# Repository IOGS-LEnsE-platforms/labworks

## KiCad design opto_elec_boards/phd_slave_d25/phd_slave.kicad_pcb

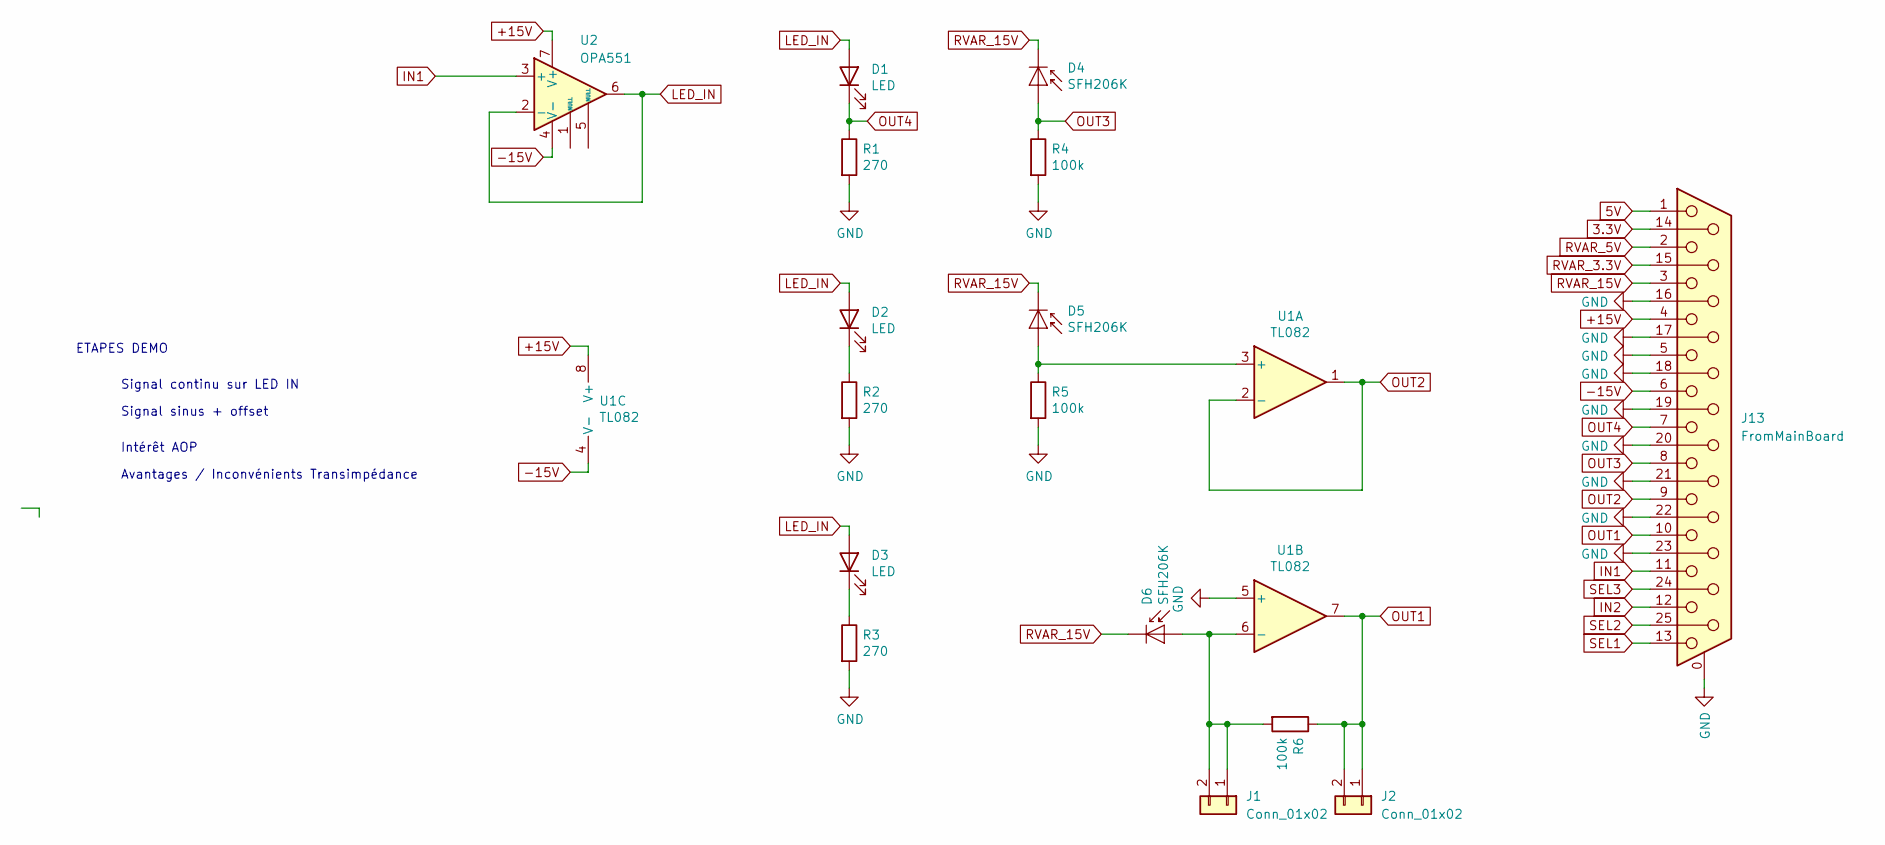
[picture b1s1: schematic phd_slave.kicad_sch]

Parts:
D1, D2, D3: LED; LED_D5.0mm_Horizontal_O3.81mm_Z9.0mm
D4, D5, D6: SFH206K; Osram_SFH206_2
J1, J2: Conn_01x02; PinSocket_1x02_P2.54mm_Vertical
J13: FromMainBoard; DSUB-25_Socket_Horizontal_P2.77x2.84mm_EdgePinOffset7.70mm_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
R1, R2, R3: 270; R_Axial_DIN0309_L9.0mm_D3.2mm_P12.70mm_Horizontal
R4, R5, R6: 100k; R_Axial_DIN0309_L9.0mm_D3.2mm_P12.70mm_Horizontal
U1: TL082; DIP-8_W7.62mm_LongPads
U2: OPA551; DIP-8_W7.62mm_LongPads

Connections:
3.3V: J13.14
5V: J13.1
+15V: J13.4, U1.8 (V+), U2.7 (V+)
-15V: J13.6, U1.4 (V-), U2.4 (V-)
GND: J13.0 (PAD), J13.5, J13.16, J13.17, J13.18, J13.19, J13.20, J13.21, J13.22, J13.23, R1.2, R2.2, R3.2, R4.2, R5.2, U1.5 (+)
IN1: J13.11, U2.3 (+)
IN2: J13.12
LED_IN: D1.2 (A), D2.2 (A), D3.2 (A), U2.2 (-), U2.6
unnamed: D2.1 (K), R2.1
unnamed: D3.1 (K), R3.1
unnamed: D5.2 (A), R5.1, U1.3 (+)
unnamed: D6.2 (A), J1.1, J1.2, R6.2, U1.6 (-)
OUT1: J2.1, J2.2, J13.10, R6.1, U1.7
OUT2: J13.9, U1.1, U1.2 (-)
OUT3: D4.2 (A), J13.8, R4.1
OUT4: D1.1 (K), J13.7, R1.1
RVAR_3.3V: J13.15
RVAR_5V: J13.2
RVAR_15V: D4.1 (K), D5.1 (K), D6.1 (K), J13.3
SEL1: J13.13
SEL2: J13.25
SEL3: J13.24

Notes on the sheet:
Signal continu sur LED IN
ETAPES DEMO
Intérêt AOP
Avantages / Inconvénients Transimpédance
Signal sinus + offset

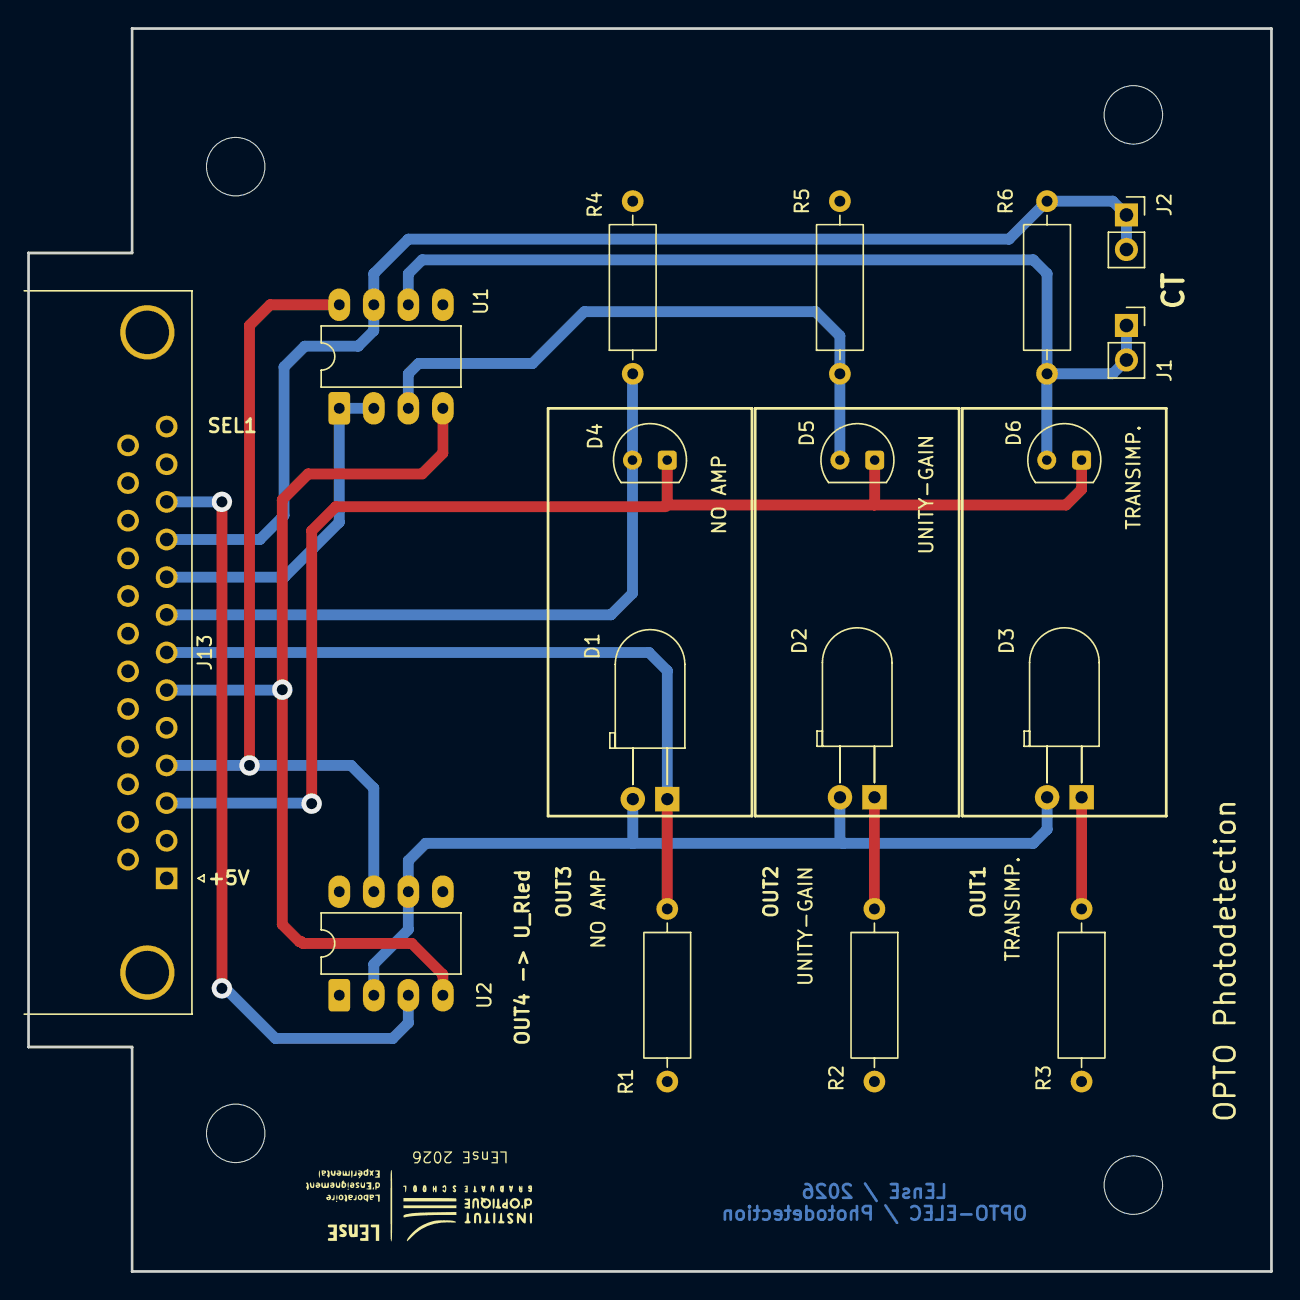
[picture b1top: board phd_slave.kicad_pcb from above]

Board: 2 copper layers, 91.4 x 91.4 mm, 21 parts (0 on the bottom side), 14 nets.

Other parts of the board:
M4a, M4b, M4c, M4d: MountingHole_4.3mm_M4

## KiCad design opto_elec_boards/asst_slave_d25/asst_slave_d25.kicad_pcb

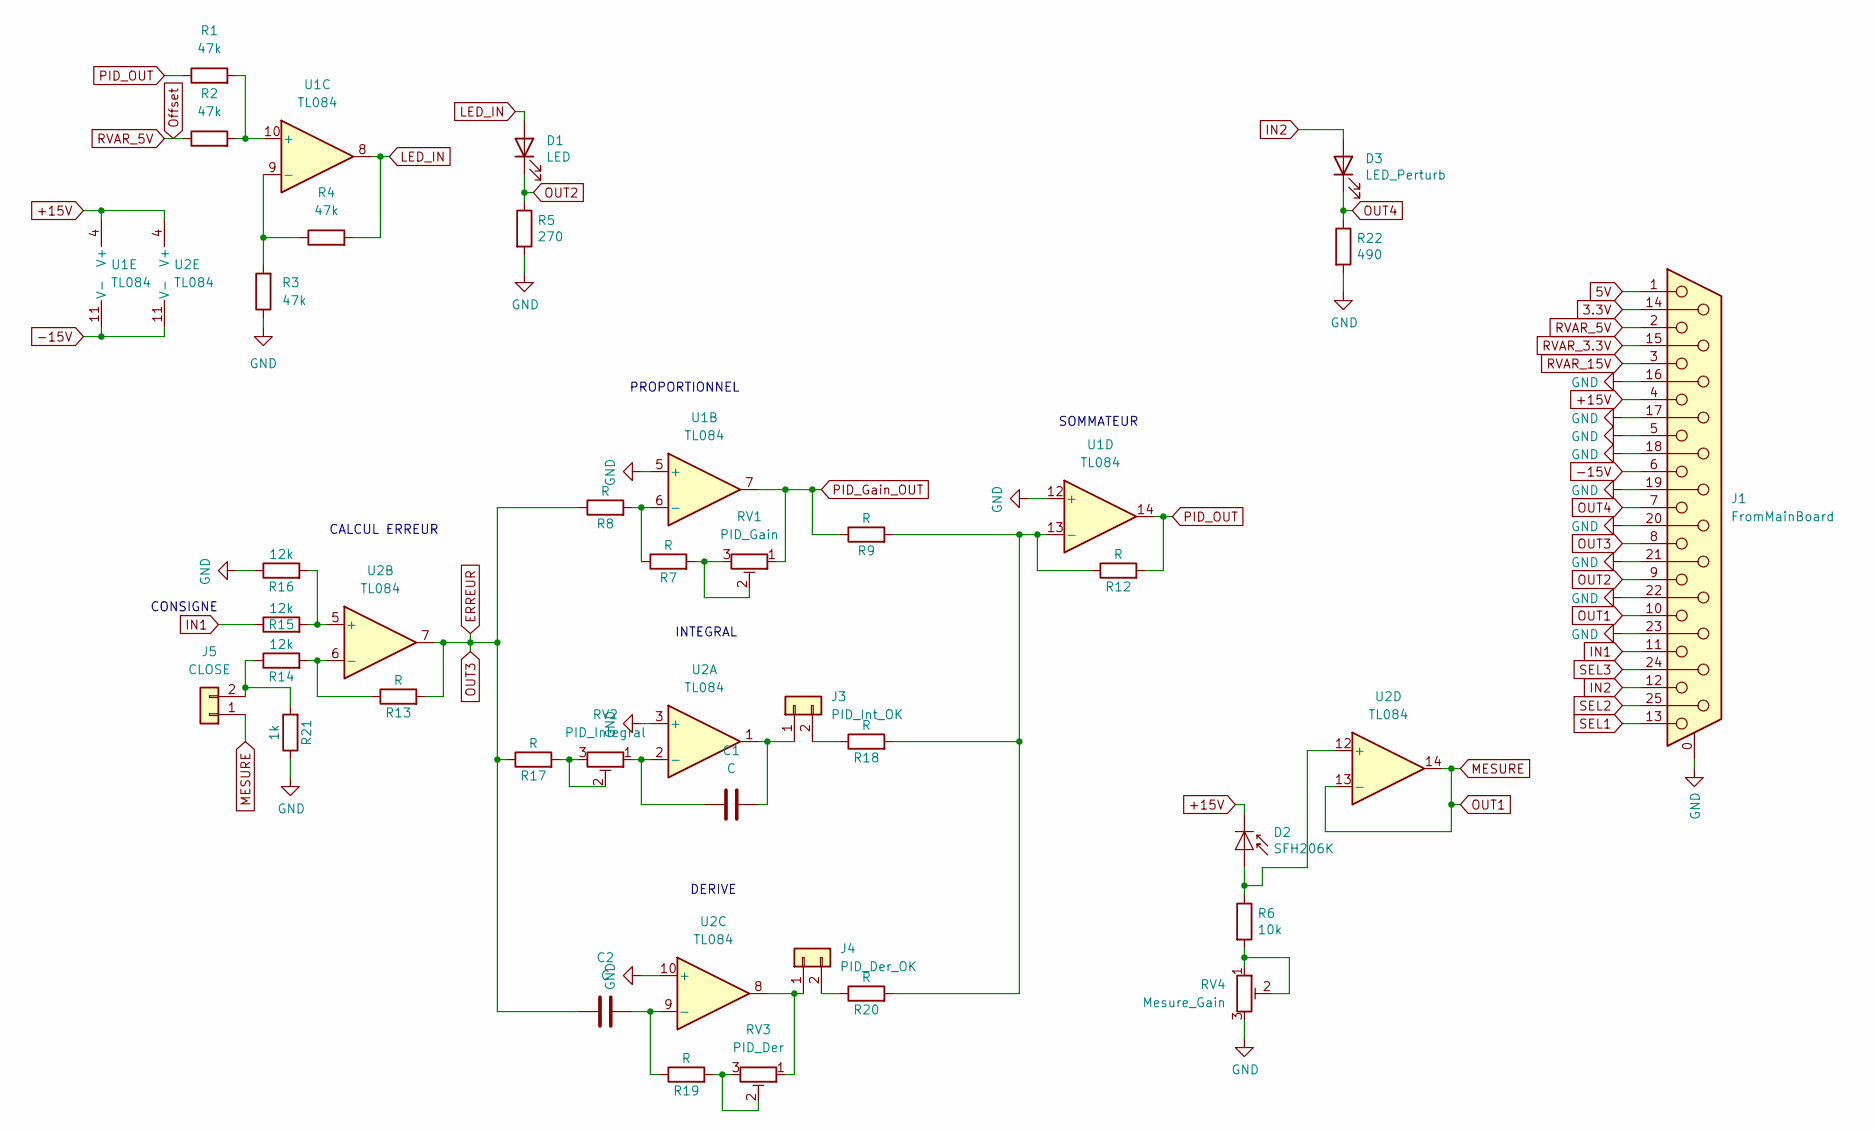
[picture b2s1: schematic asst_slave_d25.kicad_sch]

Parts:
C1, C2: C; C_R_Multi
D1: LED; LED_D10.0mm
D2: SFH206K; Osram_SFH206_2
D3: LED_Perturb; LED_D5.0mm_Horizontal_O3.81mm_Z9.0mm
J1: FromMainBoard; DSUB-25_Socket_Horizontal_P2.77x2.84mm_EdgePinOffset7.70mm_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
J3: PID_Int_OK; PinSocket_1x02_P2.54mm_Vertical
J4: PID_Der_OK; PinSocket_1x02_P2.54mm_Vertical
J5: CLOSE; PinSocket_1x02_P2.54mm_Vertical
R1, R2, R3, R4: 47k; R_Axial_DIN0207_L6.3mm_D2.5mm_P10.16mm_Horizontal
R5: 270; R_Axial_DIN0207_L6.3mm_D2.5mm_P10.16mm_Horizontal
R6: 10k; R_Axial_DIN0207_L6.3mm_D2.5mm_P10.16mm_Horizontal
R7, R8, R9, R12, R13, R17, R18, R19, R20: R; R_Axial_DIN0207_L6.3mm_D2.5mm_P10.16mm_Horizontal
R14, R15, R16: 12k; R_Axial_DIN0207_L6.3mm_D2.5mm_P10.16mm_Horizontal
R21: 1k; R_Axial_DIN0207_L6.3mm_D2.5mm_P10.16mm_Horizontal
R22: 490; R_Axial_DIN0207_L6.3mm_D2.5mm_P10.16mm_Horizontal
RV1: PID_Gain; Potentiometer_Bourns_3386P_Vertical
RV2: PID_Integral; Potentiometer_Bourns_3386P_Vertical
RV3: PID_Der; Potentiometer_Bourns_3386P_Vertical
RV4: Mesure_Gain; Potentiometer_Bourns_3386P_Vertical
U1, U2: TL084; DIP-14_W7.62mm_Socket_LongPads

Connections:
3.3V: J1.14
5V: J1.1
+15V: D2.1 (K), J1.4, U1.4 (V+), U2.4 (V+)
-15V: J1.6, U1.11 (V-), U2.11 (V-)
ERREUR: C2.1, J1.8, R8.1, R13.2, R17.1, U2.7
GND: J1.0 (PAD), J1.5, J1.16, J1.17, J1.18, J1.19, J1.20, J1.21, J1.22, J1.23, R3.1, R5.2, R16.1, R21.1, R22.2, RV4.3, U1.5 (+), U1.12 (+), U2.3 (+), U2.10 (+)
IN1: J1.11, R15.1
IN2: D3.2 (A), J1.12
LED_IN: D1.2 (A), R4.2, U1.8
MESURE: J1.10, J5.1, U2.13 (-), U2.14
unnamed: D2.2 (A), R6.1, U2.12 (+)
unnamed: C1.2, J3.1, U2.1
unnamed: J3.2, R18.1
unnamed: J4.1, RV3.1, U2.8
unnamed: J4.2, R20.1
unnamed: J5.2, R14.1, R21.2
unnamed: R6.2, RV4.1, RV4.2
unnamed: R7.2, RV1.2, RV1.3
unnamed: R17.2, RV2.2, RV2.3
unnamed: R19.2, RV3.2, RV3.3
unnamed: R7.1, R8.2, U1.6 (-)
unnamed: R1.2, R2.2, U1.10 (+)
unnamed: R3.2, R4.1, U1.9 (-)
unnamed 24: R9.2, R12.1, R18.2, R20.2, U1.13 (-); also elsewhere on the board
unnamed: C1.1, RV2.1, U2.2 (-)
unnamed: R15.2, R16.2, U2.5 (+)
unnamed: R13.1, R14.2, U2.6 (-)
unnamed: C2.2, R19.1, U2.9 (-)
OUT2: D1.1 (K), J1.9, R5.1
OUT4: D3.1 (K), J1.7, R22.1
Offset: J1.2, R2.1
PID_Gain_OUT: R9.1, RV1.1, U1.7
PID_OUT: R1.1, R12.2, U1.14
RVAR_3.3V: J1.15
RVAR_15V: J1.3
SEL1: J1.13
SEL2: J1.25
SEL3: J1.24

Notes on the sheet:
DERIVE
CALCUL ERREUR
SOMMATEUR
CONSIGNE
INTEGRAL
PROPORTIONNEL

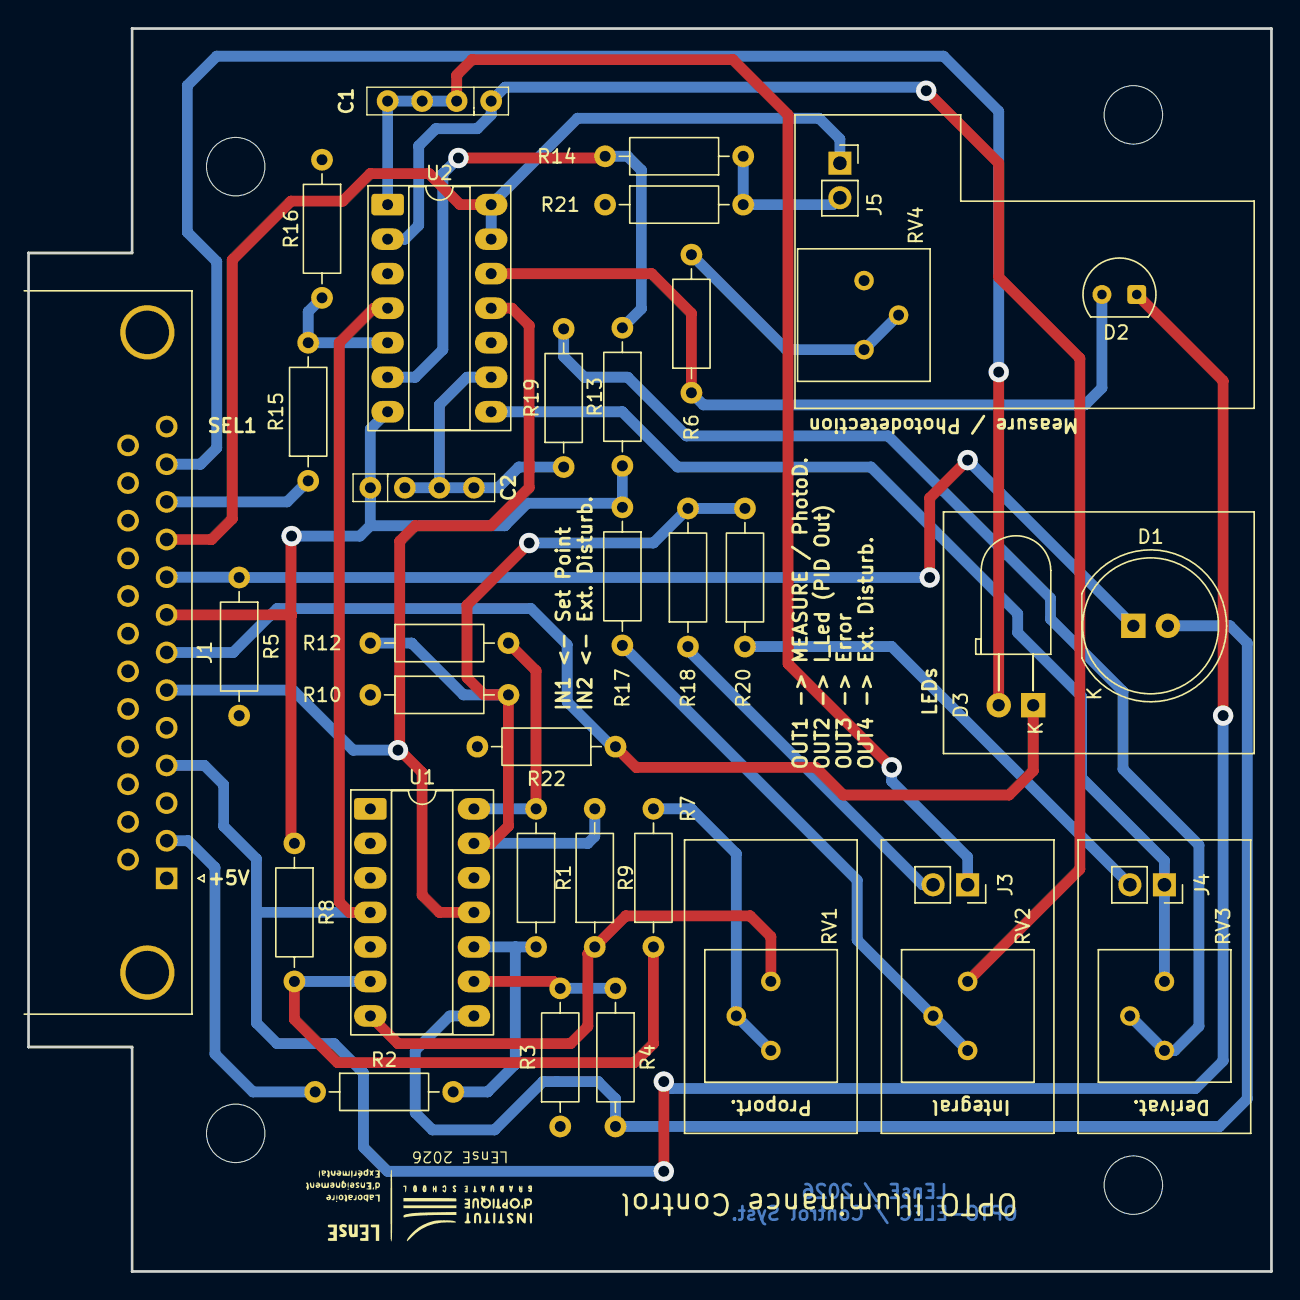
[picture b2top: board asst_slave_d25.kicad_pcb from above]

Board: 2 copper layers, 91.4 x 91.4 mm, 40 parts (0 on the bottom side), 31 nets.

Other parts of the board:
M4a, M4b, M4c, M4d: MountingHole_4.3mm_M4
R10: R; R_Axial_DIN0207_L6.3mm_D2.5mm_P10.16mm_Horizontal

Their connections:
unnamed 24: R10.2; also elsewhere on the board

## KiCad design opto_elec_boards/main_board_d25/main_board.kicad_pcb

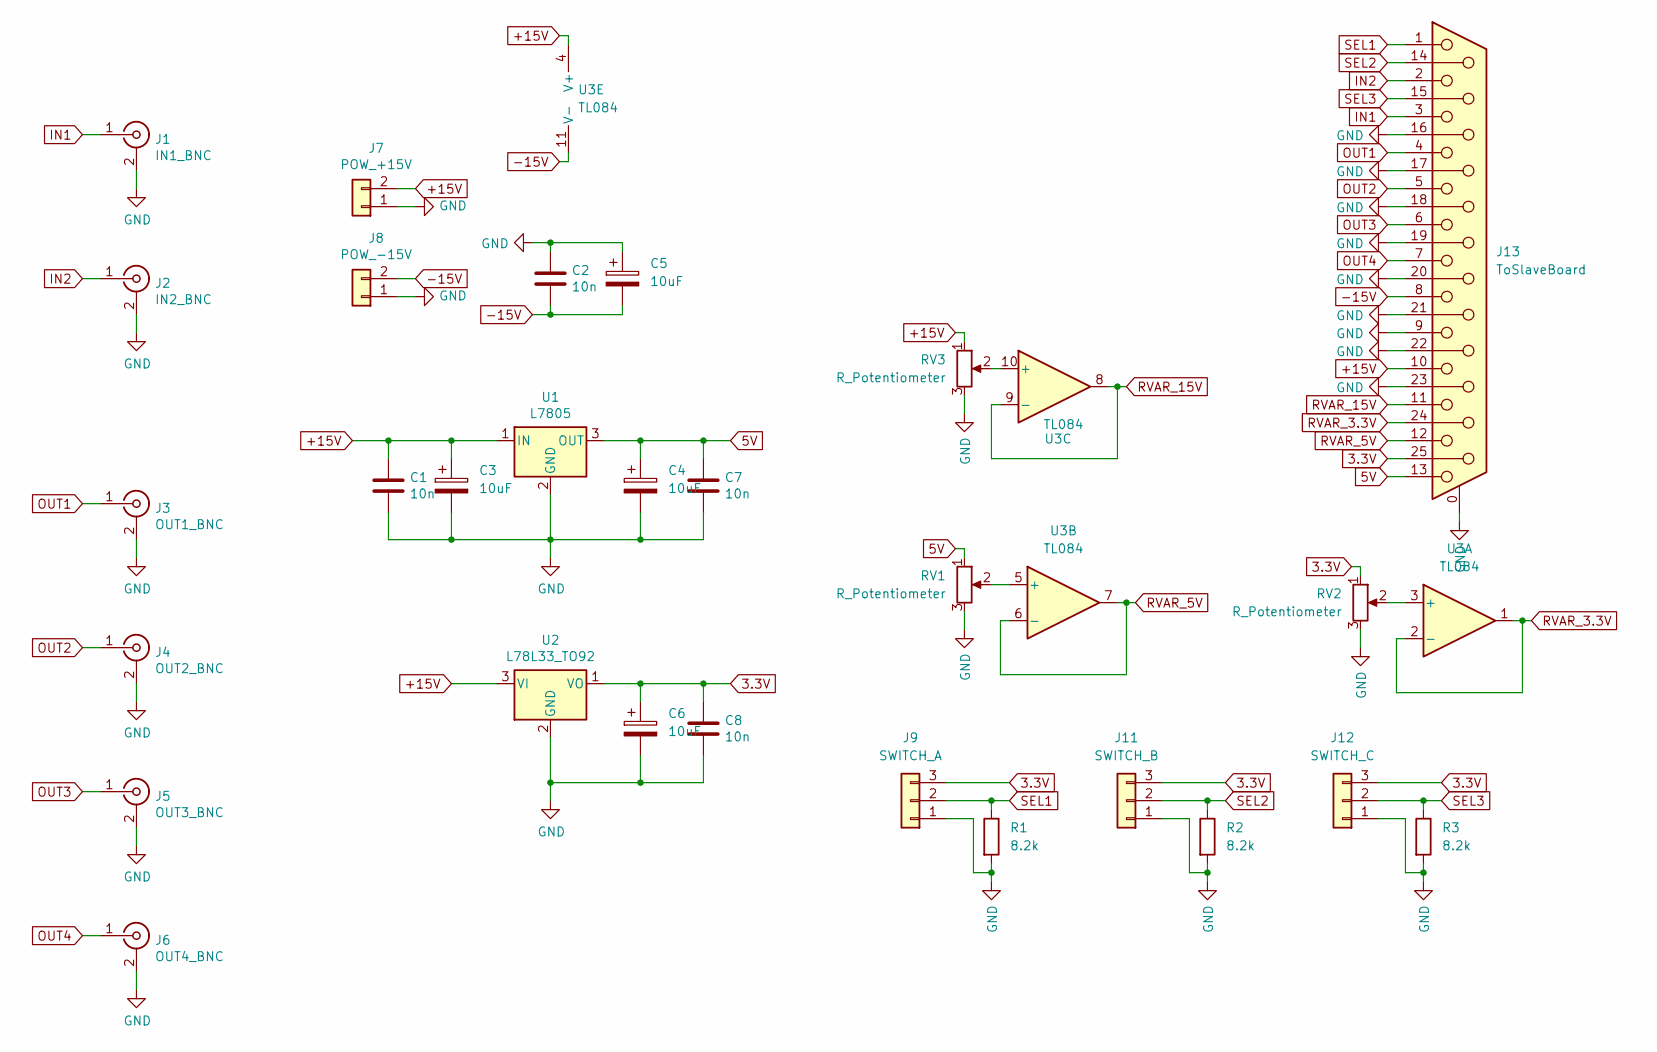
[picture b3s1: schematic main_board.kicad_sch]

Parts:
C1, C2, C7, C8: 10n; C_Disc_D10.0mm_W2.5mm_P5.00mm
C3, C4, C5, C6: 10uF; CP_Radial_D5.0mm_P2.50mm
J1: IN1_BNC; PinHeader_1x02_P2.54mm_Vertical
J2: IN2_BNC; PinHeader_1x02_P2.54mm_Vertical
J3: OUT1_BNC; PinHeader_1x02_P2.54mm_Vertical
J4: OUT2_BNC; PinHeader_1x02_P2.54mm_Vertical
J5: OUT3_BNC; PinHeader_1x02_P2.54mm_Vertical
J6: OUT4_BNC; PinHeader_1x02_P2.54mm_Vertical
J7: POW_+15V; PinSocket_1x02_P2.54mm_Vertical
J8: POW_-15V; PinSocket_1x02_P2.54mm_Vertical
J9: SWITCH_A; PinSocket_1x03_P2.54mm_Vertical
J11: SWITCH_B; PinSocket_1x03_P2.54mm_Vertical
J12: SWITCH_C; PinSocket_1x03_P2.54mm_Vertical
J13: ToSlaveBoard; DSUB-25_Socket_Horizontal_P2.77x2.84mm_EdgePinOffset4.94mm_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
R1, R2, R3: 8.2k; R_Axial_DIN0207_L6.3mm_D2.5mm_P10.16mm_Horizontal
RV1, RV2, RV3: R_Potentiometer; PinHeader_1x03_P2.54mm_Vertical
U1: L7805; TO-220-3_Vertical
U2: L78L33_TO92; TO-92_Inline_Wide
U3: TL084; DIP-14_W7.62mm_Socket_LongPads

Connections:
3.3V: C6.1, C8.1, J9.3, J11.3, J12.3, J13.25, RV2.1, U2.1 (VO)
5V: C4.1, C7.1, J13.13, RV1.1, U1.3 (OUT)
+15V: C1.1, C3.1, J7.2, J13.10, RV3.1, U1.1 (IN), U2.3 (VI), U3.4 (V+)
-15V: C2.2, C5.2, J8.2, J13.8, U3.11 (V-)
GND: C1.2, C2.1, C3.2, C4.2, C5.1, C6.2, C7.2, C8.2, J1.2 (Ext), J2.2 (Ext), J3.2 (Ext), J4.2 (Ext), J5.2 (Ext), J6.2 (Ext), J7.1, J8.1, J9.1, J11.1, J12.1, J13.0 (PAD), J13.9, J13.16, J13.17, J13.18, J13.19, J13.20, J13.21, J13.22, J13.23, R1.2, R2.2, R3.2, RV1.3, RV2.3, RV3.3, U1.2 (GND), U2.2 (GND)
IN1: J1.1 (In), J13.3
IN2: J2.1 (In), J13.2
unnamed: RV2.2, U3.3 (+)
unnamed: RV1.2, U3.5 (+)
unnamed: RV3.2, U3.10 (+)
OUT1: J3.1 (In), J13.4
OUT2: J4.1 (In), J13.5
OUT3: J5.1 (In), J13.6
OUT4: J6.1 (In), J13.7
RVAR_3.3V: J13.24, U3.1, U3.2 (-)
RVAR_5V: J13.12, U3.6 (-), U3.7
RVAR_15V: J13.11, U3.8, U3.9 (-)
SEL1: J9.2, J13.1, R1.1
SEL2: J11.2, J13.14, R2.1
SEL3: J12.2, J13.15, R3.1

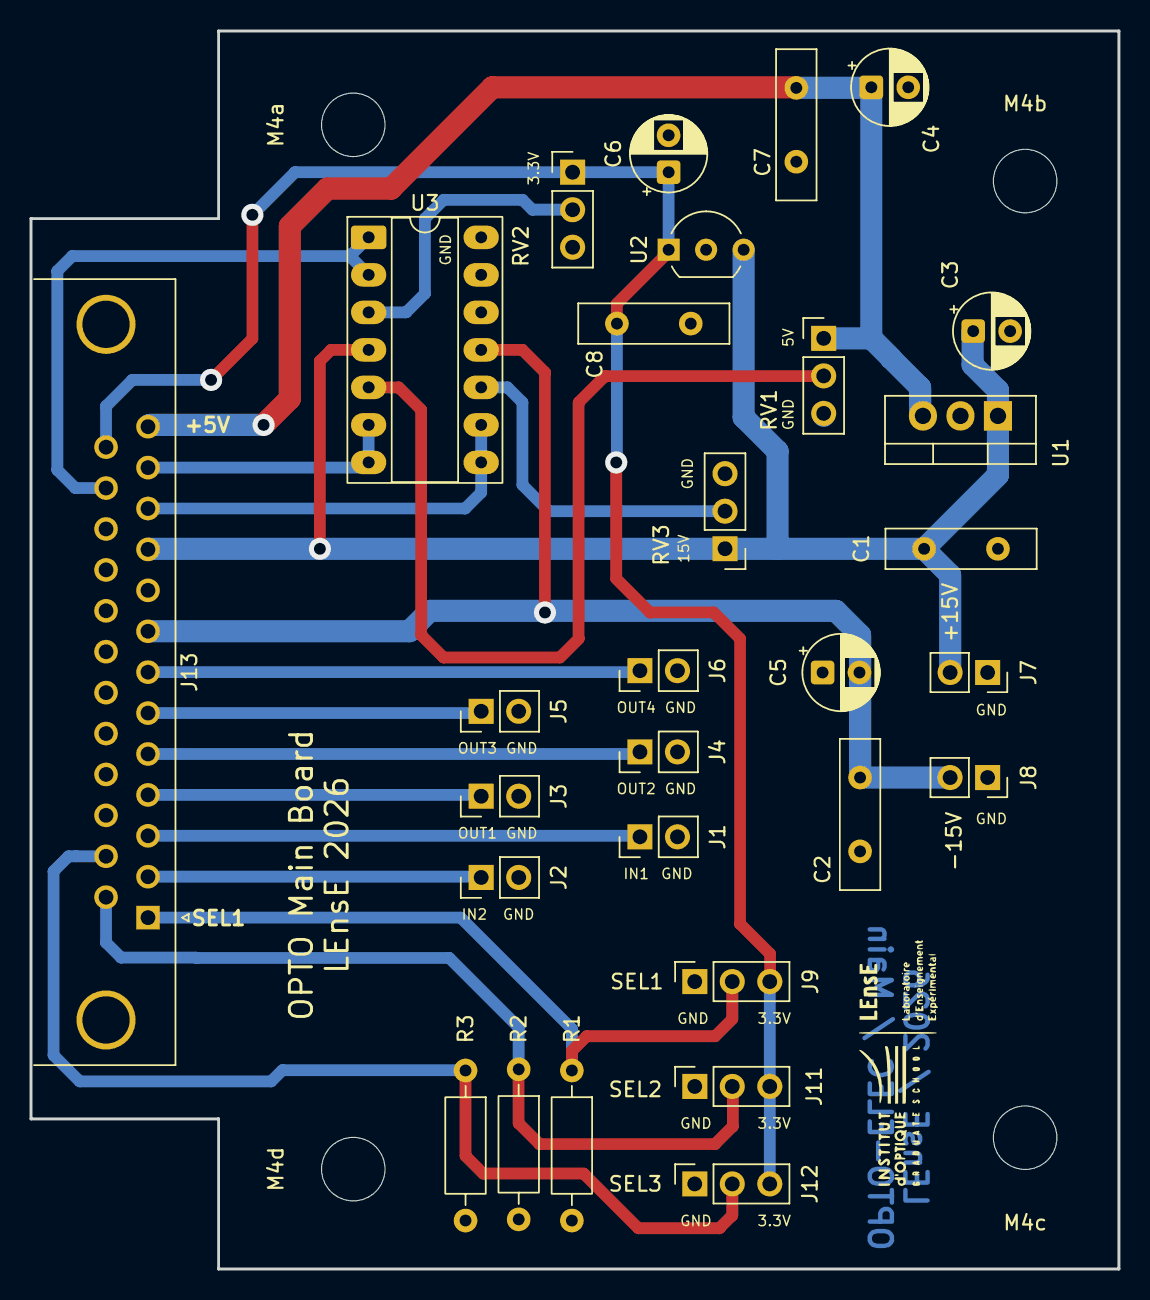
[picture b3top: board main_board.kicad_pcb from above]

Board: 2 copper layers, 73.7 x 83.8 mm, 33 parts (0 on the bottom side), 20 nets.

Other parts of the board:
M4a, M4b, M4c, M4d: MountingHole_4.3mm_M4

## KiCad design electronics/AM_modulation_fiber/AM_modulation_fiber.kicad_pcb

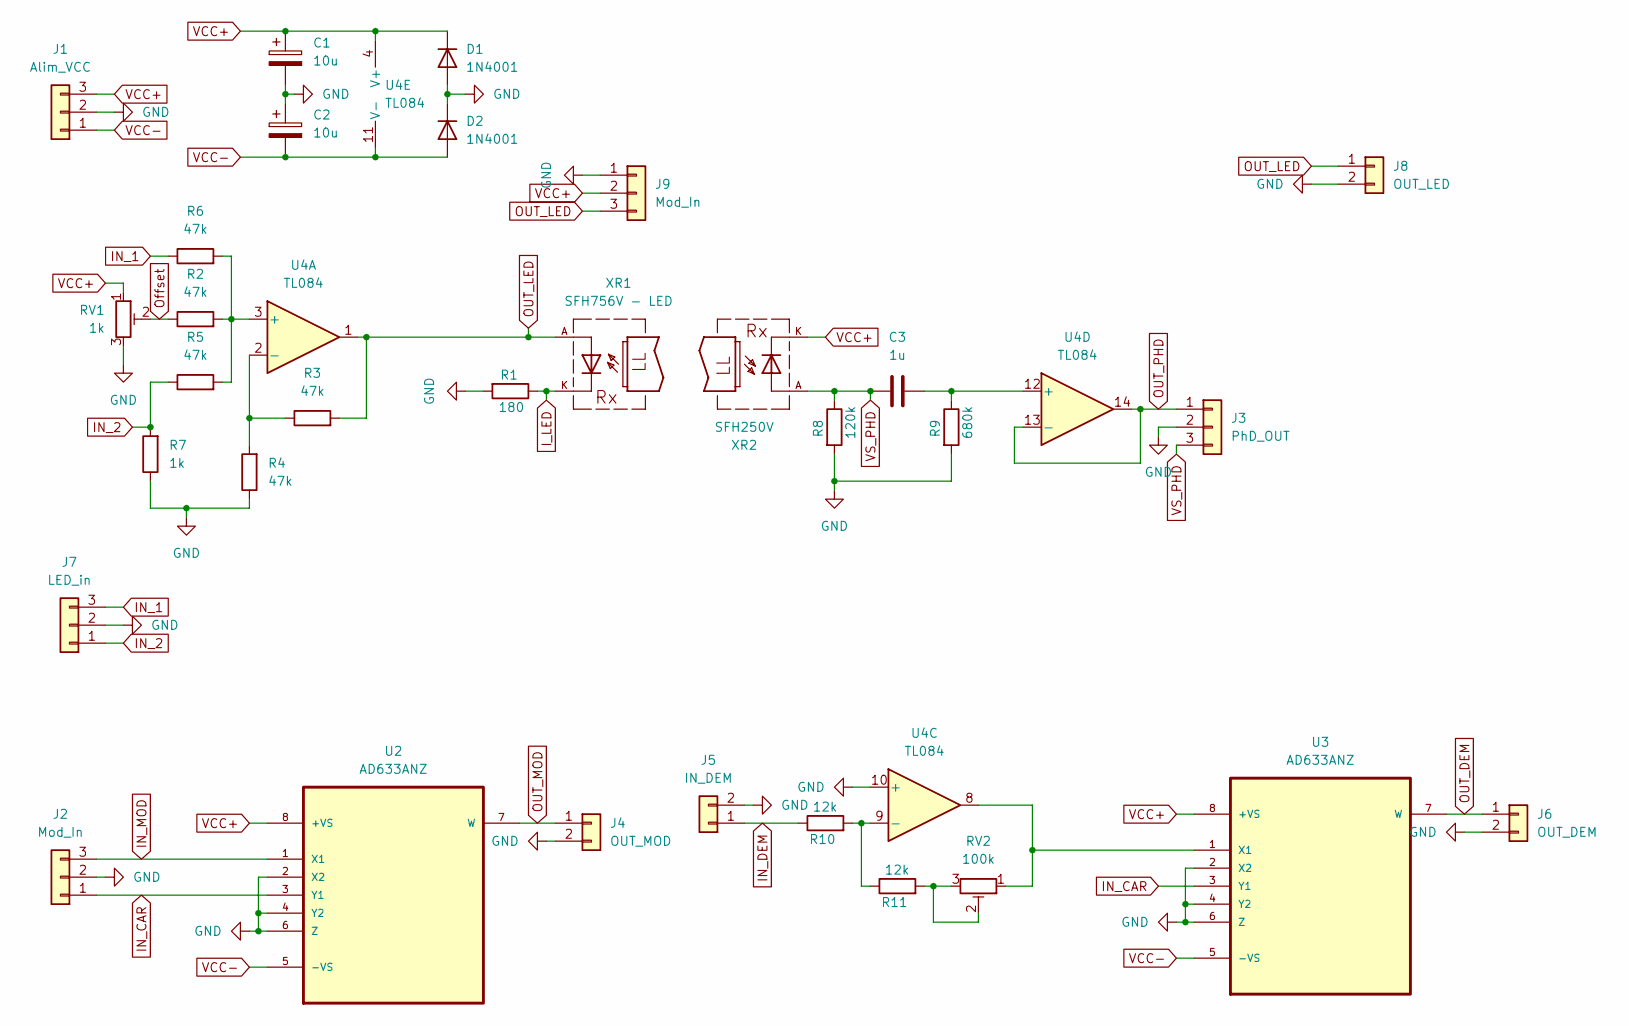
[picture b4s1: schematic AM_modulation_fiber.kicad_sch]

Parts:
C1, C2: 10u; CP_Radial_D6.3mm_P2.50mm
C3: 1u; C_Rect_L7.0mm_W4.5mm_P5.00mm
D1, D2: 1N4001; D_DO-41_SOD81_P10.16mm_Horizontal
J1: Alim_VCC; PinHeader_1x03_P2.54mm_Vertical
J2, J9: Mod_In; PinHeader_1x03_P2.54mm_Vertical
J3: PhD_OUT; PinHeader_1x03_P2.54mm_Vertical
J4: OUT_MOD; PinHeader_1x02_P2.54mm_Vertical
J5: IN_DEM; PinHeader_1x02_P2.54mm_Vertical
J6: OUT_DEM; PinHeader_1x02_P2.54mm_Vertical
J7: LED_in; PinHeader_1x03_P2.54mm_Vertical
J8: OUT_LED; PinHeader_1x02_P2.54mm_Vertical
R1: 180; R_Axial_DIN0207_L6.3mm_D2.5mm_P10.16mm_Horizontal
R2, R3, R4, R5, R6: 47k; R_Axial_DIN0207_L6.3mm_D2.5mm_P10.16mm_Horizontal
R7: 1k; R_Axial_DIN0207_L6.3mm_D2.5mm_P10.16mm_Horizontal
R8: 120k; R_Axial_DIN0207_L6.3mm_D2.5mm_P10.16mm_Horizontal
R9: 680k; R_Axial_DIN0207_L6.3mm_D2.5mm_P10.16mm_Horizontal
R10, R11: 12k; R_Axial_DIN0207_L6.3mm_D2.5mm_P10.16mm_Horizontal
RV1: 1k; Potentiometer_Bourns_3386P_Vertical
RV2: 100k; Potentiometer_Bourns_3386P_Vertical
U2, U3: AD633ANZ; DIP-8_W7.62mm_Socket_LongPads; MPN AD633ANZ
U4: TL084; DIP-14_W7.62mm_Socket_LongPads
XR1: SFH756V - LED; SFH-V; MPN SP000063852
XR2: SFH250V; SFH-V; MPN SP000063852

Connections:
GND: C1.2, C2.1, D1.2 (A), D2.1 (K), J1.2, J2.2, J3.2, J4.2, J5.2, J6.2, J7.2, J8.2, J9.1, R1.2, R4.1, R7.1, R8.2, R9.2, RV1.3, U2.2 (X2), U2.4 (Y2), U2.6 (Z), U3.2 (X2), U3.4 (Y2), U3.6 (Z), U4.10 (+)
IN_1: J7.3, R6.1
IN_2: J7.1, R5.1, R7.2
IN_CAR: J2.1, U2.3 (Y1), U3.3 (Y1)
IN_DEM: J5.1, R10.1
IN_MOD: J2.3, U2.1 (X1)
I_LED: R1.1, XR1.K
unnamed: R11.2, RV2.2, RV2.3
unnamed: RV2.1, U3.1 (X1), U4.8
unnamed: R2.2, R5.2, R6.2, U4.3 (+)
unnamed: R3.1, R4.2, U4.2 (-)
unnamed: R10.2, R11.1, U4.9 (-)
unnamed: C3.2, R9.1, U4.12 (+)
OUT_DEM: J6.1, U3.7 (W)
OUT_LED: J8.1, J9.3, R3.2, U4.1, XR1.A
OUT_MOD: J4.1, U2.7 (W)
OUT_PHD: J3.1, U4.13 (-), U4.14
Offset: R2.1, RV1.2
VCC+: C1.1, D1.1 (K), J1.3, J9.2, RV1.1, U2.8 (+VS), U3.8 (+VS), U4.4 (V+), XR2.K
VCC-: C2.2, D2.2 (A), J1.1, U2.5 (-VS), U3.5 (-VS), U4.11 (V-)
VS_PHD: C3.1, J3.3, R8.1, XR2.A

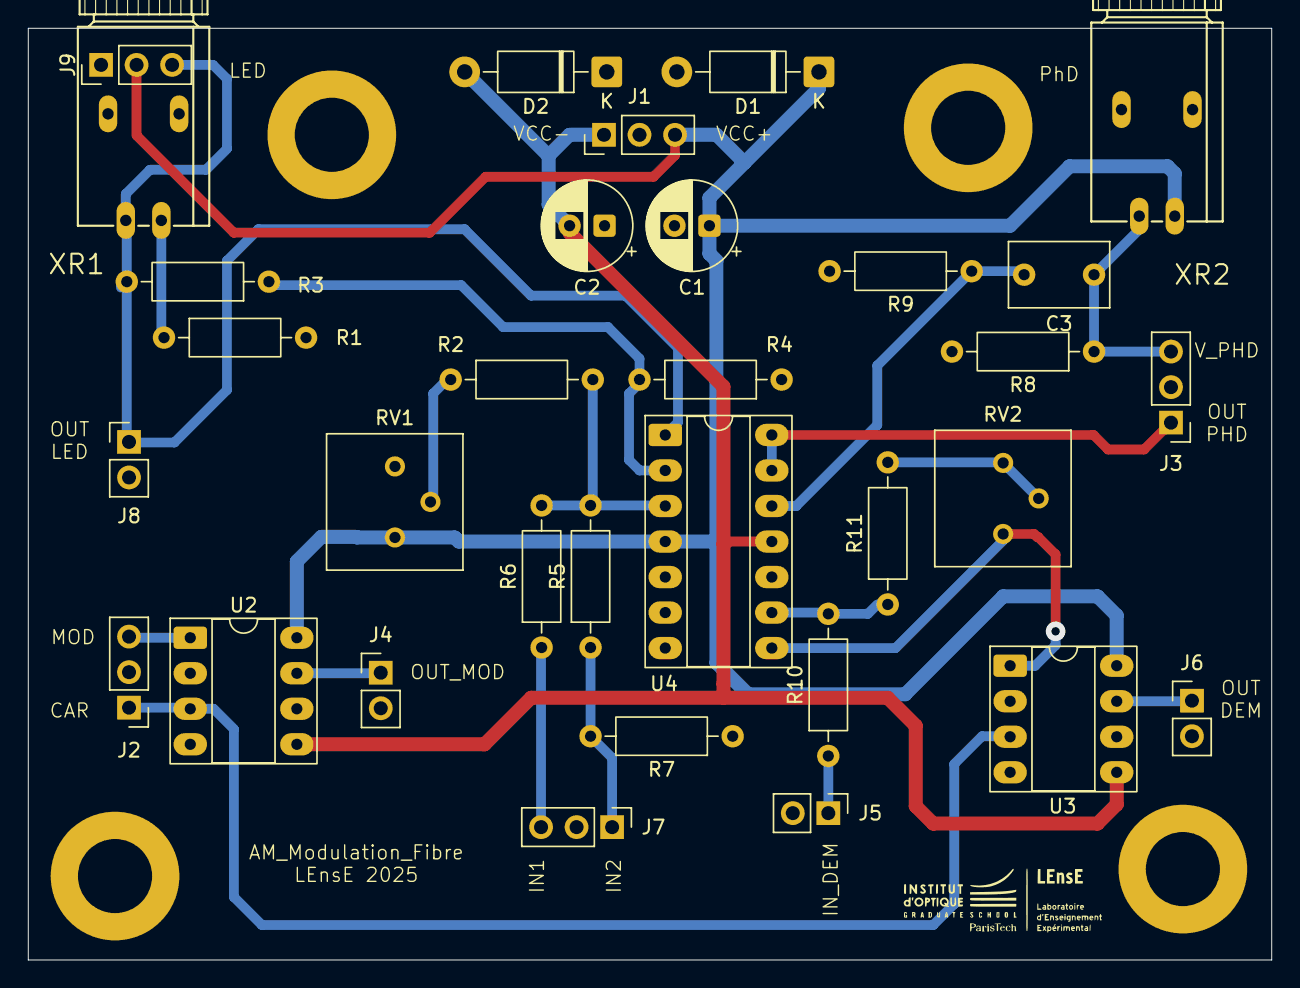
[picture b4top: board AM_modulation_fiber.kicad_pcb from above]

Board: 2 copper layers, 88.9 x 66.6 mm, 32 parts (0 on the bottom side), 21 nets.

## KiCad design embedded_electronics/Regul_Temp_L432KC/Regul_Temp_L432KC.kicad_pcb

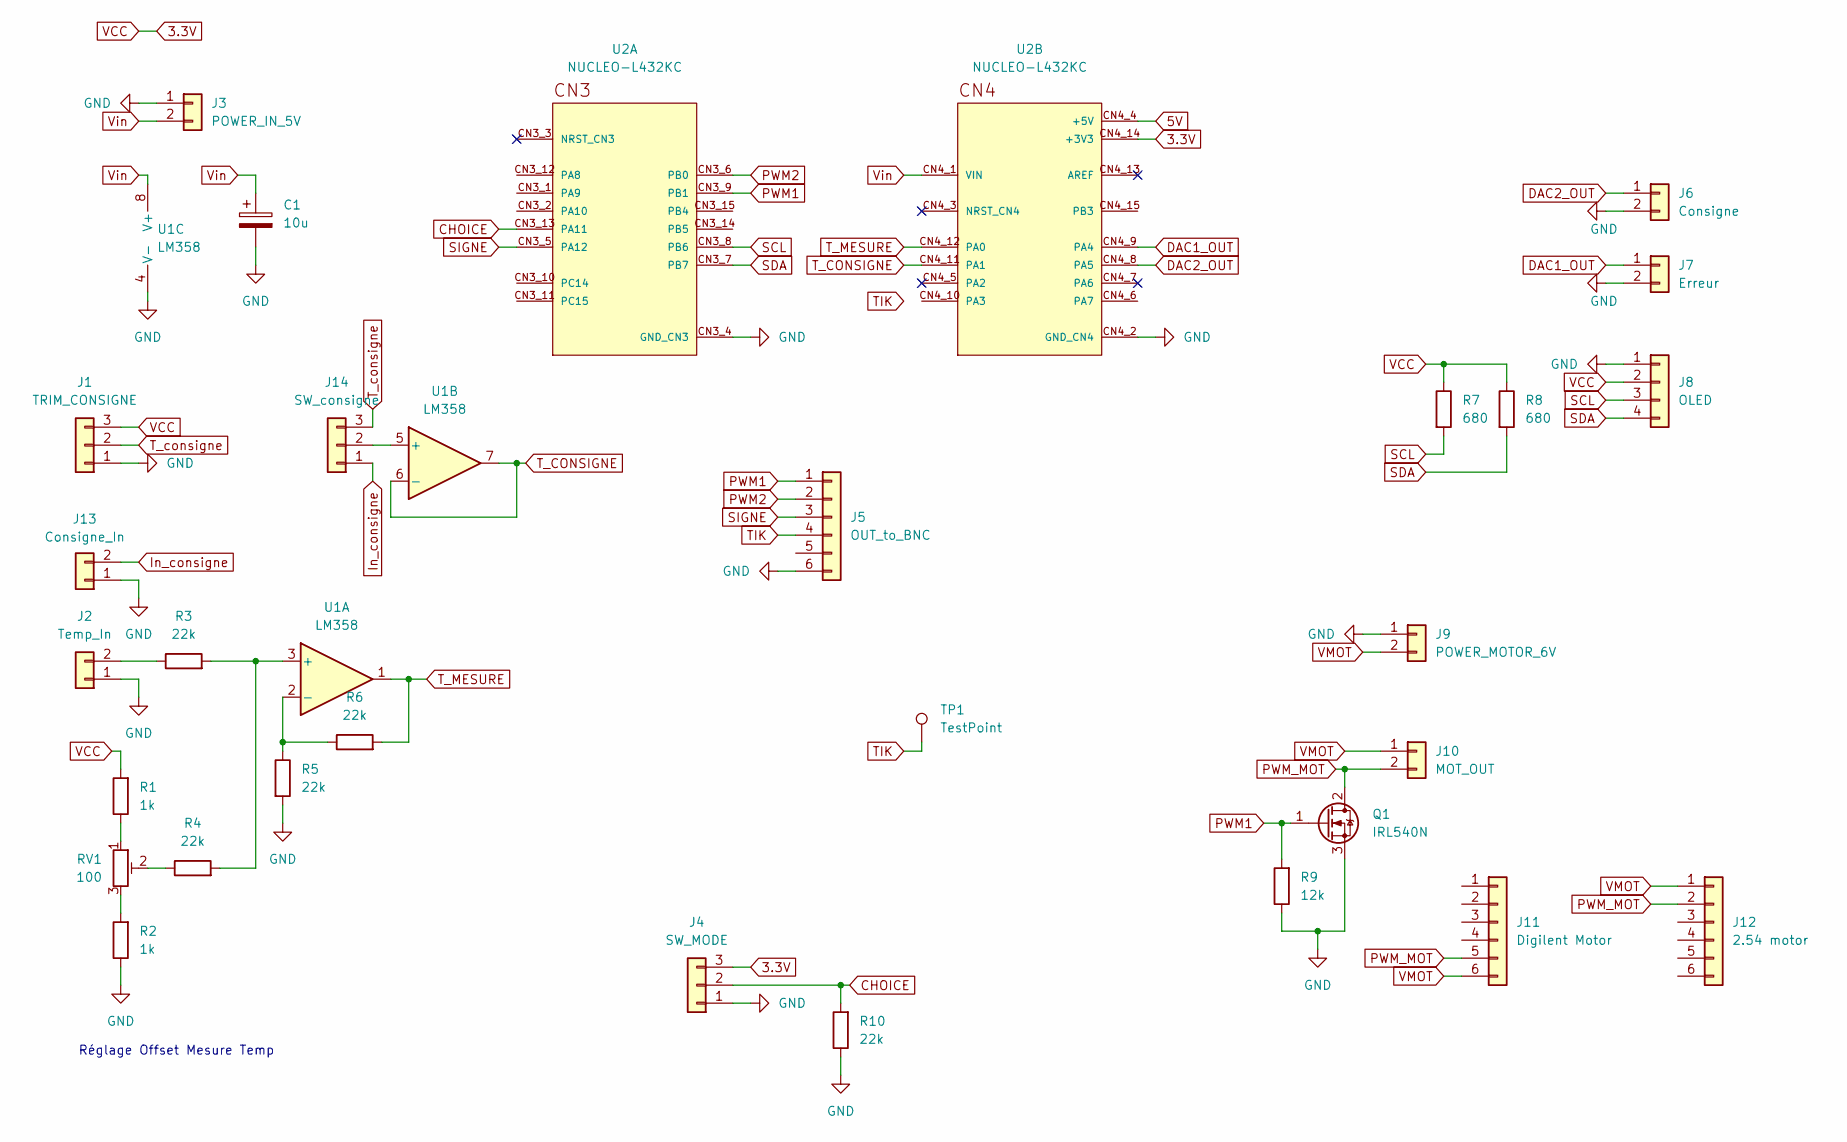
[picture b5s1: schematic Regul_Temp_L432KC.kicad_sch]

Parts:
C1: 10u; CP_Radial_D5.0mm_P2.50mm
J1: TRIM_CONSIGNE; PinSocket_1x03_P2.54mm_Vertical
J2: Temp_In; PinSocket_1x02_P2.54mm_Vertical
J3: POWER_IN_5V; PinSocket_1x02_P2.54mm_Vertical
J4: SW_MODE; PinSocket_1x03_P2.54mm_Vertical
J5: OUT_to_BNC; PinHeader_1x06_P2.54mm_Vertical
J6: Consigne; PinSocket_1x02_P2.54mm_Vertical
J7: Erreur; PinSocket_1x02_P2.54mm_Vertical
J8: OLED; PinHeader_1x04_P2.54mm_Vertical
J9: POWER_MOTOR_6V; PinSocket_1x02_P2.54mm_Vertical
J10: MOT_OUT; TerminalBlock_Phoenix_MKDS-3-2-5.08_1x02_P5.08mm_Horizontal
J11: Digilent Motor; JST_PH_S6B-PH-K_1x06_P2.00mm_Horizontal
J12: 2.54 motor; PinHeader_1x06_P2.54mm_Vertical
J13: Consigne_In; PinSocket_1x02_P2.54mm_Vertical
J14: SW_consigne; PinSocket_1x03_P2.54mm_Vertical
Q1: IRL540N; TO-220-3_Vertical
R1, R2: 1k; R_Axial_DIN0207_L6.3mm_D2.5mm_P10.16mm_Horizontal
R3, R4, R5, R6, R10: 22k; R_Axial_DIN0207_L6.3mm_D2.5mm_P10.16mm_Horizontal
R7, R8: 680; R_Axial_DIN0207_L6.3mm_D2.5mm_P10.16mm_Horizontal
R9: 12k; R_Axial_DIN0207_L6.3mm_D2.5mm_P10.16mm_Horizontal
RV1: 100; Potentiometer_Bourns_3386P_Vertical
TP1: TestPoint; TestPoint_THTPad_2.5x2.5mm_Drill1.2mm
U1: LM358; DIP-8_W7.62mm_LongPads
U2: NUCLEO-L432KC; MODULE_NUCLEO-L432KC; PARTREV N/A

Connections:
3.3V: J1.3, J4.3, J8.2, R1.2, R7.1, R8.1, U2.CN4_14 (+3V3)
5V: U2.CN4_4 (+5V)
CHOICE: J4.2, R10.2, U2.CN3_13 (PA11)
DAC1_OUT: J7.1, U2.CN4_9 (PA4)
DAC2_OUT: J6.1, U2.CN4_8 (PA5)
GND: C1.2, J1.1, J2.1, J3.1, J4.1, J5.6, J6.2, J7.2, J8.1, J9.1, J13.1, Q1.3 (S), R2.1, R5.2, R9.1, R10.1, U1.4 (V-), U2.CN3_4 (GND_CN3), U2.CN4_2 (GND_CN4)
In_consigne: J13.2, J14.1
unnamed: J2.2, R3.1
unnamed: J14.2, U1.5 (+)
unnamed: R1.1, RV1.1
unnamed: R2.2, RV1.3
unnamed: R4.1, RV1.2
unnamed: R3.2, R4.2, U1.3 (+)
unnamed: R5.1, R6.1, U1.2 (-)
PWM1: J5.1, Q1.1 (G), R9.2, U2.CN3_9 (PB1)
PWM2: J5.2, U2.CN3_6 (PB0)
PWM_MOT: J10.2, J11.5, J12.2, Q1.2 (D)
SCL: J8.3, R7.2, U2.CN3_8 (PB6)
SDA: J8.4, R8.2, U2.CN3_7 (PB7)
SIGNE: J5.3, U2.CN3_5 (PA12)
TIK: J5.4, TP1.1, U2.CN4_5 (PA2)
T_CONSIGNE: U1.6 (-), U1.7, U2.CN4_11 (PA1)
T_MESURE: R6.2, U1.1, U2.CN4_12 (PA0)
T_consigne: J1.2, J14.3
VMOT: J9.2, J10.1, J11.6, J12.1
Vin: C1.1, J3.2, U1.8 (V+), U2.CN4_1 (VIN)

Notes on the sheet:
Réglage Offset Mesure Temp
